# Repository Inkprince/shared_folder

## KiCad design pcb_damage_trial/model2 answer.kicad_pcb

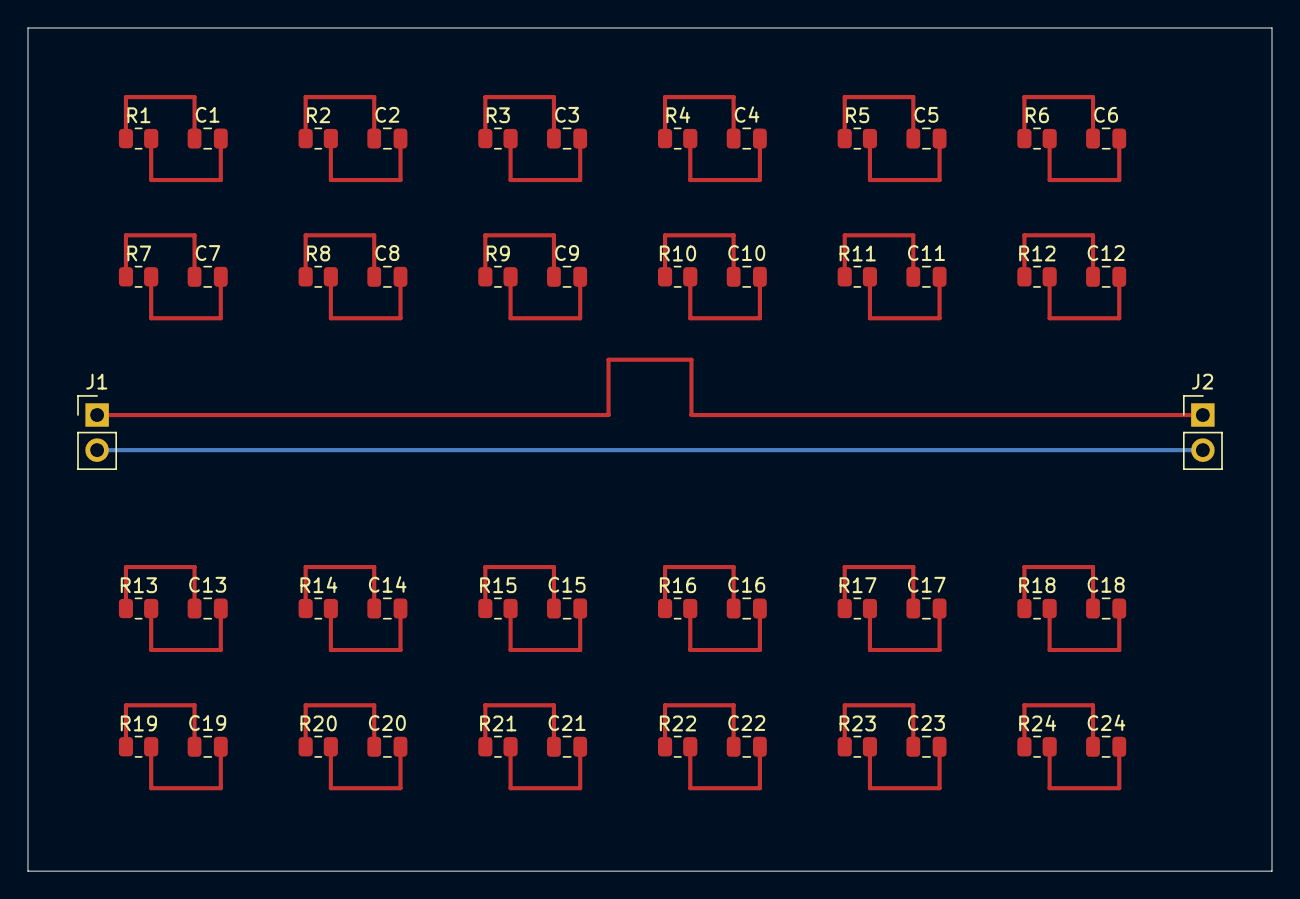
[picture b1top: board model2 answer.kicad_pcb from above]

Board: 2 copper layers, 90.0 x 61.0 mm, 50 parts (0 on the bottom side), 50 nets.

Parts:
C1, C2, C3, C4, C5, C6, C7, C8, C9, C10, C11, C12, C13, C14, C15, C16, C17, C18, C19, C20, C21, C22, C23, C24: 10n; C_0805_2012Metric
J1, J2: SIG/GND; PinHeader_1x02_P2.54mm_Vertical
R1, R7, R13, R19: 1k; R_0805_2012Metric
R2, R8, R14, R20: 2k; R_0805_2012Metric
R3, R9, R15, R21: 3k; R_0805_2012Metric
R4, R10, R16, R22: 4k; R_0805_2012Metric
R5, R11, R17, R23: 5k; R_0805_2012Metric
R6, R12, R18, R24: 6k; R_0805_2012Metric

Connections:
CELL1_HI: C1.1, R1.1
CELL1_LO: C1.2, R1.2
CELL2_HI: C2.1, R2.1
CELL2_LO: C2.2, R2.2
CELL3_HI: C3.1, R3.1
CELL3_LO: C3.2, R3.2
CELL4_HI: C4.1, R4.1
CELL4_LO: C4.2, R4.2
CELL5_HI: C5.1, R5.1
CELL5_LO: C5.2, R5.2
CELL6_HI: C6.1, R6.1
CELL6_LO: C6.2, R6.2
CELL7_HI: C7.1, R7.1
CELL7_LO: C7.2, R7.2
CELL8_HI: C8.1, R8.1
CELL8_LO: C8.2, R8.2
CELL9_HI: C9.1, R9.1
CELL9_LO: C9.2, R9.2
CELL10_HI: C10.1, R10.1
CELL10_LO: C10.2, R10.2
CELL11_HI: C11.1, R11.1
CELL11_LO: C11.2, R11.2
CELL12_HI: C12.1, R12.1
CELL12_LO: C12.2, R12.2
CELL13_HI: C13.1, R13.1
CELL13_LO: C13.2, R13.2
CELL14_HI: C14.1, R14.1
CELL14_LO: C14.2, R14.2
CELL15_HI: C15.1, R15.1
CELL15_LO: C15.2, R15.2
CELL16_HI: C16.1, R16.1
CELL16_LO: C16.2, R16.2
CELL17_HI: C17.1, R17.1
CELL17_LO: C17.2, R17.2
CELL18_HI: C18.1, R18.1
CELL18_LO: C18.2, R18.2
CELL19_HI: C19.1, R19.1
CELL19_LO: C19.2, R19.2
CELL20_HI: C20.1, R20.1
CELL20_LO: C20.2, R20.2
CELL21_HI: C21.1, R21.1
CELL21_LO: C21.2, R21.2
CELL22_HI: C22.1, R22.1
CELL22_LO: C22.2, R22.2
CELL23_HI: C23.1, R23.1
CELL23_LO: C23.2, R23.2
CELL24_HI: C24.1, R24.1
CELL24_LO: C24.2, R24.2
GND: J1.2, J2.2
SIG: J1.1, J2.1

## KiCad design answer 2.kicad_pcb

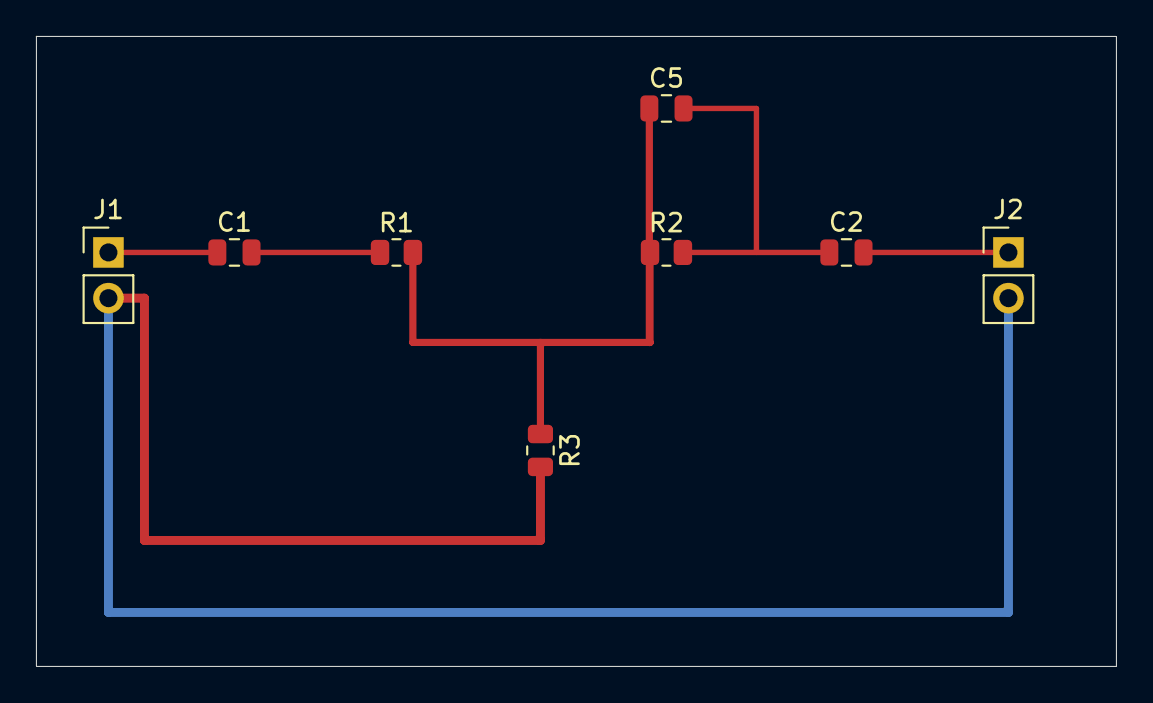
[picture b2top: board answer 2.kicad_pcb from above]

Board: 2 copper layers, 60.0 x 35.0 mm, 8 parts (0 on the bottom side), 6 nets.

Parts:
C1: 47n; C_0805_2012Metric
C2: 10n; C_0805_2012Metric
C5: 33n; C_0805_2012Metric
J1: IN/GND; PinHeader_1x02_P2.54mm_Vertical
J2: OUT/GND; PinHeader_1x02_P2.54mm_Vertical
R1, R2: 16k; R_0805_2012Metric
R3: 22k; R_0805_2012Metric

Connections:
A: C5.1, R1.2, R2.1, R3.1
B: C2.1, C5.2, R2.2
GND: J1.2, J2.2, R3.2
IN: C1.1, J1.1
N1: C1.2, R1.1
OUT: C2.2, J2.1
